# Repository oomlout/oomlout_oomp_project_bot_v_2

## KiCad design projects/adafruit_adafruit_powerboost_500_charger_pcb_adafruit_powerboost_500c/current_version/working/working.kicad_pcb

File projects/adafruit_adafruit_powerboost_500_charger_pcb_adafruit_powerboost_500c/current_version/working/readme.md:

# adafruit_powerboost_500_charger_pcb
 
## summary 
* id: adafruit_adafruit_powerboost_500_charger_pcb_adafruit_powerboost_500c
* user: adafruit
* name: adafruit_powerboost_500_charger_pcb
* board: adafruit_powerboost_500c
* repo: https://github.com/adafruit/Adafruit-PowerBoost-500-Charger-PCB

* src_file_repo_sch: 
* src_file_repo_sch_link: https://github.com/adafruit/Adafruit-PowerBoost-500-Charger-PCB/tree/master/
* full details link: https://github.com/oomlout/oomlout_oomp_project_bot_v_2/tree/main/projects/adafruit_adafruit_powerboost_500_charger_pcb_adafruit_powerboost_500c/current_version/working  

## schematic  
  
[schematic (pdf)](working_schematic.pdf) 

## pcb  

[board (pdf)](working.pdf)  

## working_bom
| Id | Designator | Footprint | Quantity | Designation | Supplier and ref |  | None | 
| --- | --- | --- | --- | --- | --- | --- | --- | 
| 1 | U$26 | SYMBOL_MINUS | 1 |  |  |  | [''] | 
| 2 | R3,R1 | 0805-NO | 2 | 1.87Mohm |  |  | [''] | 
| 3 | U$13,U$25 | SYMBOL_PLUS | 2 |  |  |  | [''] | 
| 4 | R13,R2 | 0805-NO | 2 | 340K |  |  | [''] | 
| 5 | U$12,U$10 | MOUNTINGHOLE_2.5_PLATED | 2 | MOUNTINGHOLE2.5 |  |  | [''] | 
| 6 | R6 | 0805-NO | 1 | 470 |  |  | [''] | 
| 7 | R10,R12 | 0805-NO | 2 | 49.9K 1% |  |  | [''] | 
| 8 | FID3,FID2 | FIDUCIAL_1MM | 2 | FIDUCIAL" |  |  | [''] | 
| 9 | C2 | 0805-NO | 1 | 2.2uF |  |  | [''] | 
| 10 | PWR0 | CHIPLED_0805_NOOUTLINE | 1 | BLUE |  |  | [''] | 
| 11 | C6 | 0805-NO | 1 | 10ÂµF |  |  | [''] | 
| 12 | LED4 | CHIPLED_0805_NOOUTLINE | 1 | GREEN |  |  | [''] | 
| 13 | R9,R11 | 0805-NO | 2 | 75K 1% |  |  | [''] | 
| 14 | Q1 | SC59-BEC | 1 | MMUN2133LT1G |  |  | [''] | 
| 15 | R7,R20,R5 | 0805-NO | 3 | 1K |  |  | [''] | 
| 16 | U1 | PVQFN-16 | 1 | TPS61090RSAR |  |  | [''] | 
| 17 | B1 | JSTPH2 | 1 | 1.8-5V |  |  | [''] | 
| 18 | U2 | SOT23-5 | 1 | MCP73831T-2ACI/OT |  |  | [''] | 
| 19 | X2 | 4UCONN_20329 | 1 | microUSB |  |  | [''] | 
| 20 | C5 | EIA3528-21_B-R | 1 | 100uF/6V |  |  | [''] | 
| 21 | R4 | 0805-NO | 1 | 200K |  |  | [''] | 
| 22 | JP1 | 1X06-CLEANBIG | 1 |  |  |  | [''] | 
| 23 | JP2 | 1X02_ROUND | 1 |  |  |  | [''] | 
| 24 | R8 | 0805-NO | 1 | 2k |  |  | [''] | 
| 25 | CN1 | USB_HOST-PTH | 1 | USBA_FEMALE |  |  | [''] | 
| 26 | LBO0 | CHIPLED_0805_NOOUTLINE | 1 | RED |  |  | [''] | 
| 27 | L1 | INDUCTOR_5X5MM_TDK_VLC5045 | 1 | VLC5045-6.8uH |  |  | [''] | 
| 28 | U$28 | ADAFRUIT_2.5MM | 1 |  |  |  | [''] | 
| 29 | C4 | 0805-NO | 1 | 0.1uF |  |  | [''] | 
| 30 | C1 | 0805-NO | 1 | 10uF |  |  | [''] | 
| 31 | LED3 | CHIPLED_0805_NOOUTLINE | 1 | ORANGE |  |  | [''] | 
| 32 | X1 | TERMBLOCK_1X2-3.5MM | 1 |  |  |  | [''] | 
| 33 | U$29 | ADAFRUIT_5MM | 1 |  |  |  | [''] | 

## bom_schematic
| Ref | Qnty | Value | Cmp name | Footprint | Description | Vendor | DNP | 
| --- | --- | --- | --- | --- | --- | --- | --- | 
| B1 | 1 | 1.8-5V | BATTERY | working:JSTPH2 |  |  |  | 
| C1 | 1 | 10uF | CAP_CERAMIC0805-NOOUTLINE | working:0805-NO |  |  |  | 
| C2 | 1 | 2.2uF | CAP_CERAMIC0805-NOOUTLINE | working:0805-NO |  |  |  | 
| C4 | 1 | 0.1uF | CAP_CERAMIC0805-NOOUTLINE | working:0805-NO |  |  |  | 
| C5 | 1 | 100uF/6V | CAP_TANTALUMB/3528_REFLOW | working:EIA3528-21_B-R |  |  |  | 
| C6 | 1 | 10ÂµF | CAP_CERAMIC0805-NOOUTLINE | working:0805-NO |  |  |  | 
| CN1 | 1 | USBA_FEMALE | USB_TYPEAPTHFML | working:USB_HOST-PTH |  |  |  | 
| FID2, FID3 | 2 | FIDUCIAL"" | FIDUCIAL{dblquote}{dblquote} | working:FIDUCIAL_1MM |  |  |  | 
| JP1 | 1 | PINHD-1X6CB | PINHD-1X6CB | working:1X06-CLEANBIG |  |  |  | 
| JP2 | 1 | HEADER-1X2ROUND | HEADER-1X2ROUND | working:1X02_ROUND |  |  |  | 
| L1 | 1 | VLC5045-6.8uH | INDUCTORTDK_VLC5045 | working:INDUCTOR_5X5MM_TDK_VLC5045 |  |  |  | 
| LBO0 | 1 | RED | LED0805_NOOUTLINE | working:CHIPLED_0805_NOOUTLINE |  |  |  | 
| LED3 | 1 | ORANGE | LED0805_NOOUTLINE | working:CHIPLED_0805_NOOUTLINE |  |  |  | 
| LED4 | 1 | GREEN | LED0805_NOOUTLINE | working:CHIPLED_0805_NOOUTLINE |  |  |  | 
| PWR0 | 1 | BLUE | LED0805_NOOUTLINE | working:CHIPLED_0805_NOOUTLINE |  |  |  | 
| Q1 | 1 | MMUN2133LT1G | -PNP_DRIVER-SC59-BEC | working:SC59-BEC |  |  |  | 
| R1, R3 | 2 | 1.87Mohm | RESISTOR0805_NOOUTLINE | working:0805-NO |  |  |  | 
| R2, R13 | 2 | 340K | RESISTOR0805_NOOUTLINE | working:0805-NO |  |  |  | 
| R4 | 1 | 200K | RESISTOR0805_NOOUTLINE | working:0805-NO |  |  |  | 
| R5, R7, R20 | 3 | 1K | RESISTOR0805_NOOUTLINE | working:0805-NO |  |  |  | 
| R6 | 1 | 470 | RESISTOR0805_NOOUTLINE | working:0805-NO |  |  |  | 
| R8 | 1 | 2k | RESISTOR0805_NOOUTLINE | working:0805-NO |  |  |  | 
| R9, R11 | 2 | 75K 1% | RESISTOR0805_NOOUTLINE | working:0805-NO |  |  |  | 
| R10, R12 | 2 | 49.9K 1% | RESISTOR0805_NOOUTLINE | working:0805-NO |  |  |  | 
| U1 | 1 | TPS61090RSAR | VREG_TPS6103X | working:PVQFN-16 |  |  |  | 
| U2 | 1 | MCP73831T-2ACI/OT | MCP73831/2 | working:SOT23-5 |  |  |  | 
| U$10, U$12 | 2 | MOUNTINGHOLE2.5 | MOUNTINGHOLE2.5 | working:MOUNTINGHOLE_2.5_PLATED |  |  |  | 
| X1 | 1 | TERMBLOCK_1X2 | TERMBLOCK_1X2 | working:TERMBLOCK_1X2-3.5MM |  |  |  | 
| X2 | 1 | microUSB | USBMICRO_20329 | working:4UCONN_20329 |  |  |  | 

## mounting_holes
| x | y | package | value | ref | size | 
| --- | --- | --- | --- | --- | --- | 
| 0.0 | 16.51 | MOUNTINGHOLE_2.5_PLATED | MOUNTINGHOLE2.5 | U$10 | m3 | 
| 0.0 | 0.0 | MOUNTINGHOLE_2.5_PLATED | MOUNTINGHOLE2.5 | U$12 | m3 |

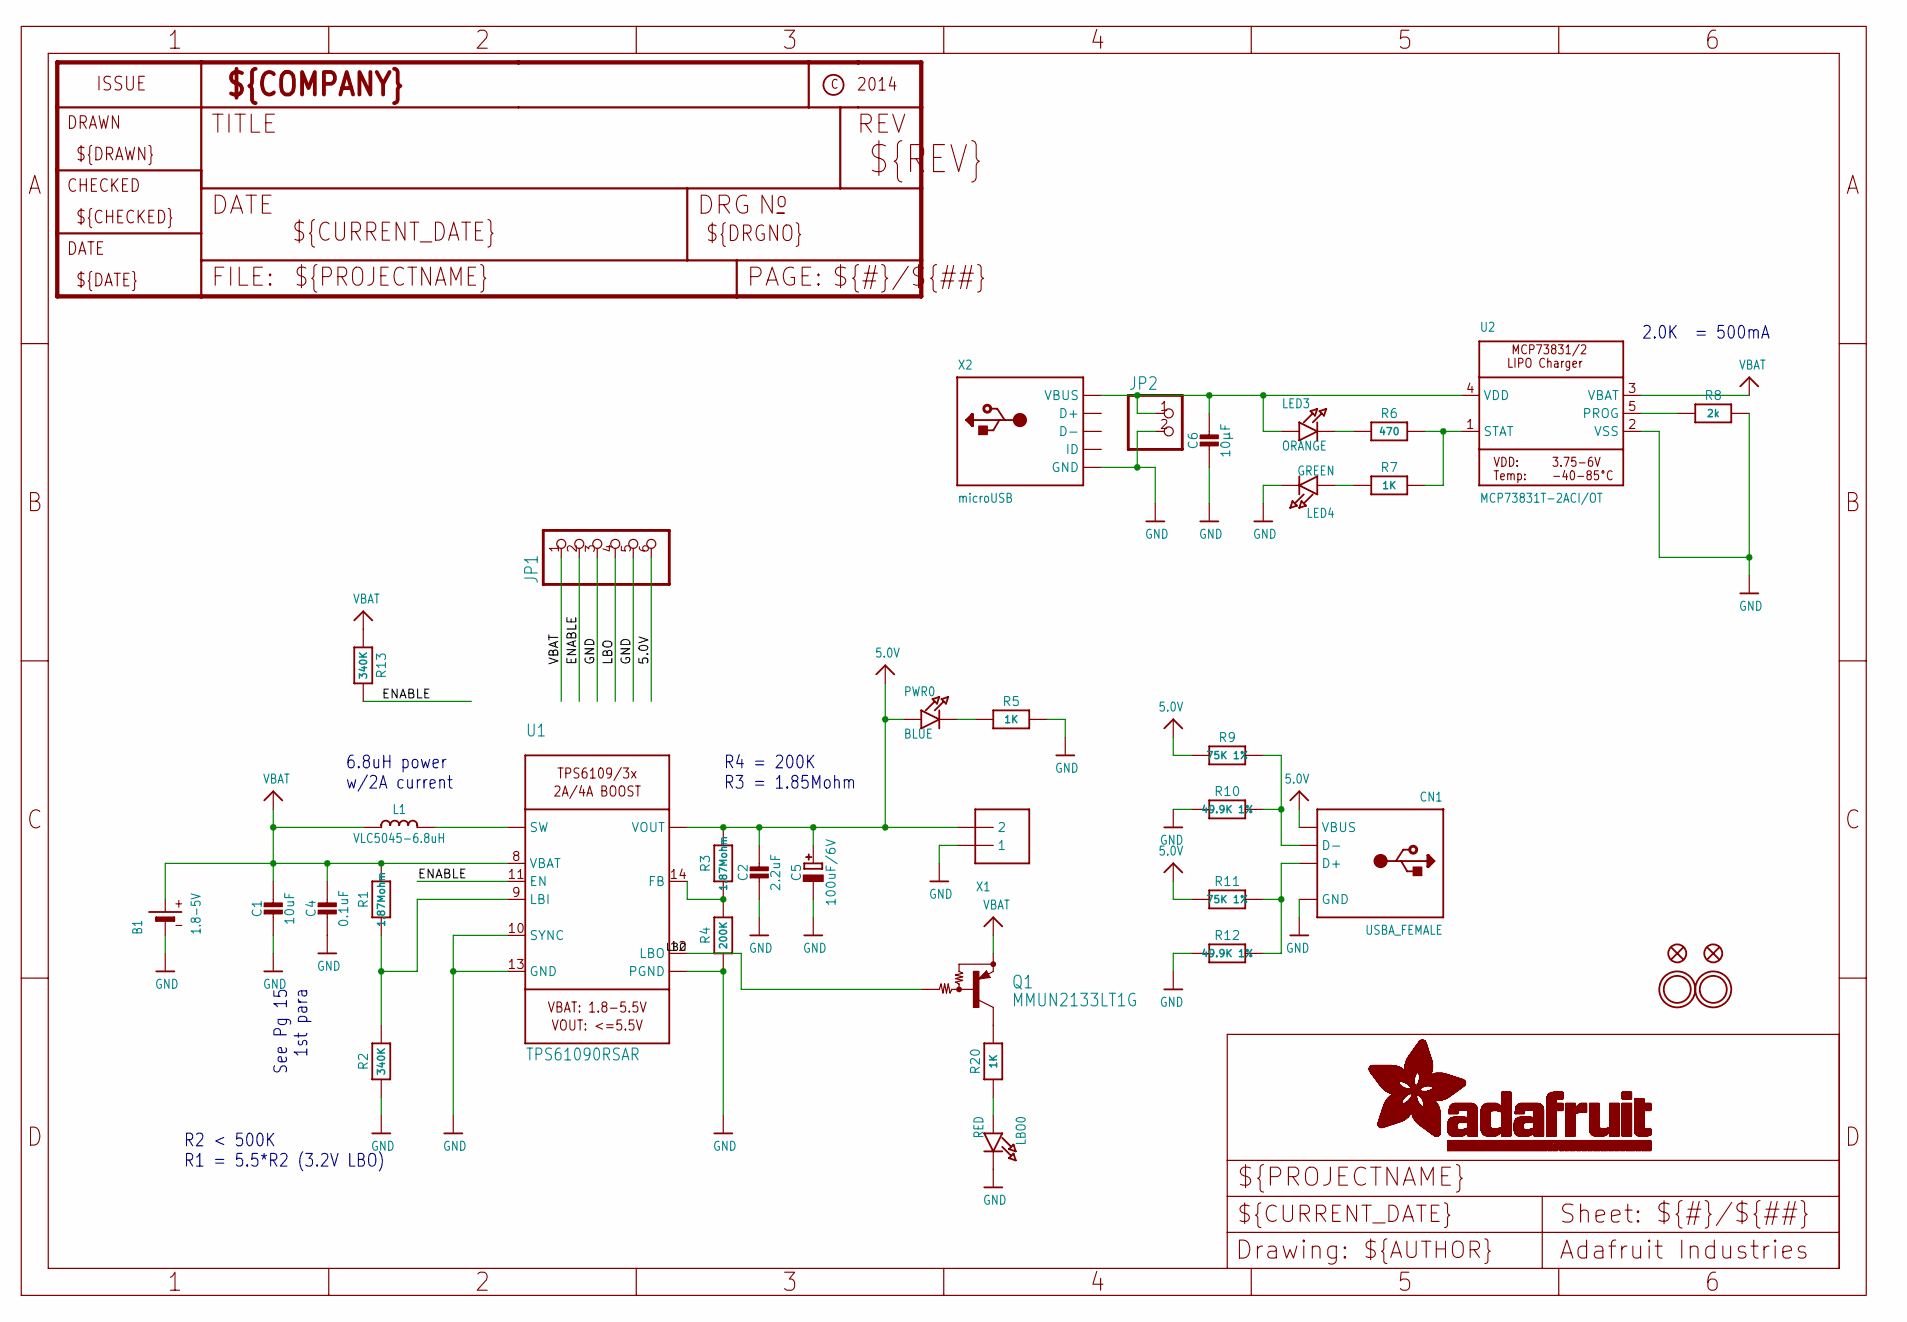
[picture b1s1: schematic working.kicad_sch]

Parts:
B1: 1.8-5V; JSTPH2
C1: 10uF; 0805-NO
C2: 2.2uF; 0805-NO
C4: 0.1uF; 0805-NO
C5: 100uF/6V; EIA3528-21_B-R
C6: 10µF; 0805-NO
CN1: USBA_FEMALE; USB_HOST-PTH
FID2, FID3: FIDUCIAL""; FIDUCIAL_1MM
JP1: PINHD-1X6CB; 1X06-CLEANBIG
JP2: HEADER-1X2ROUND; 1X02_ROUND
L1: VLC5045-6.8uH; INDUCTOR_5X5MM_TDK_VLC5045
LBO0: RED; CHIPLED_0805_NOOUTLINE
LED3: ORANGE; CHIPLED_0805_NOOUTLINE
LED4: GREEN; CHIPLED_0805_NOOUTLINE
PWR0: BLUE; CHIPLED_0805_NOOUTLINE
Q1: MMUN2133LT1G; SC59-BEC
R1, R3: 1.87Mohm; 0805-NO
R2, R13: 340K; 0805-NO
R4: 200K; 0805-NO
R5, R7, R20: 1K; 0805-NO
R6: 470; 0805-NO
R8: 2k; 0805-NO
R9, R11: 75K 1%; 0805-NO
R10, R12: 49.9K 1%; 0805-NO
U1: TPS61090RSAR; PVQFN-16
U2: MCP73831T-2ACI/OT; SOT23-5
U$10, U$12: MOUNTINGHOLE2.5; MOUNTINGHOLE_2.5_PLATED
X1: TERMBLOCK_1X2; TERMBLOCK_1X2-3.5MM
X2: microUSB; 4UCONN_20329

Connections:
5.0V: C2.1, C5.+, CN1.VBUS, JP1.6, PWR0.A, R3.2, R9.2, R11.2, U1.1 (VOUT), U1.15 (VOUT), U1.16 (VOUT), X1.2
D+: CN1.D+, R11.1, R12.1
D-: CN1.D-, R9.1, R10.1
ENABLE: JP1.2, R13.2, U1.11 (EN)
GND: B1.1 (-), C1.2, C2.2, C4.2, C5.-, C6.2, CN1.GND, JP1.3, JP1.5, JP2.2, LBO0.C, LED4.C, R2.1, R4.1, R5.2, R8.2, R10.2, R12.2, U1.5 (PGND), U1.6 (PGND), U1.7 (PGND), U1.10 (SYNC), U1.13 (GND), U1.P$18 (PGND), U1.P$19 (PGND), U1.P$20 (PGND), U1.P$21 (PGND), U1.P$22 (PGND), U1.THERMAL (PGND), U2.2 (VSS), X1.1, X2.BASE@1 (GND), X2.BASE@2 (GND), X2.GND, X2.SPRT@1 (GND), X2.SPRT@2 (GND), X2.SPRT@3 (GND), X2.SPRT@4 (GND)
LBO: JP1.4, Q1.B, U1.12 (LBO)
unnamed: L1.P$2 (2), U1.3 (SW), U1.4 (SW)
unnamed: LBO0.A, R20.1
unnamed: R1.1, R2.2, U1.9 (LBI)
unnamed: PWR0.C, R5.1
unnamed: R3.1, R4.2, U1.14 (FB)
unnamed: LED3.C, R6.1
unnamed: R6.2, R7.2, U2.1 (STAT)
unnamed: R8.1, U2.5 (PROG)
unnamed: LED4.A, R7.1
unnamed: Q1.C, R20.2
VBAT: B1.2 (+), C1.1, C4.1, JP1.1, L1.P$1 (1), Q1.E, R1.2, R13.1, U1.8 (VBAT), U2.3 (VBAT)
VDD1: C6.1, JP2.1, LED3.A, U2.4 (VDD), X2.VBUS

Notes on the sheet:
2.0K = 500mA
R4 = 200K R3 = 1.85Mohm
6.8uH power w/2A current
See Pg 15 1st para
R2 < 500K R1 = 5.5*R2 (3.2V LBO)

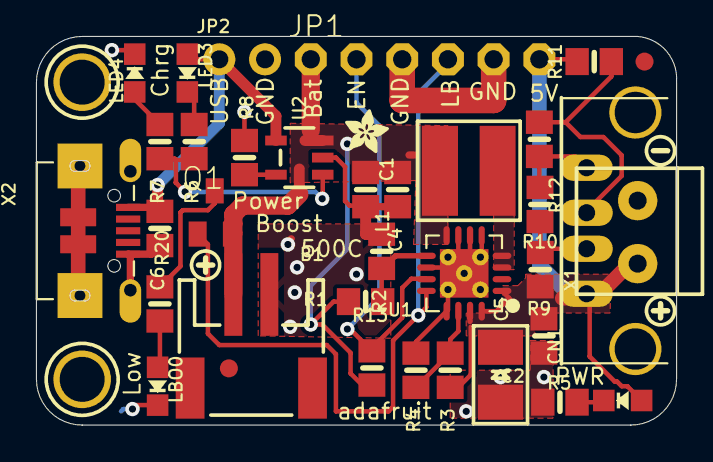
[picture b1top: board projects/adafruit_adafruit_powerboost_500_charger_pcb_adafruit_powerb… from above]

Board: 2 copper layers, 35.6 x 21.6 mm, 42 parts (1 on the bottom side), 18 nets.

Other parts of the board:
U$13, U$25: SYMBOL_PLUS
U$26: SYMBOL_MINUS
U$28: ADAFRUIT_2.5MM
U$29: ADAFRUIT_5MM

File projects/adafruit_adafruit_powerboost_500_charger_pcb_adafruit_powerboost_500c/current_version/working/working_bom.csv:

"Id";"Designator";"Footprint";"Quantity";"Designation";"Supplier and ref";
1;"U$26";"SYMBOL_MINUS";1;"";;;
2;"R3,R1";"0805-NO";2;"1.87Mohm";;;
3;"U$13,U$25";"SYMBOL_PLUS";2;"";;;
4;"R13,R2";"0805-NO";2;"340K";;;
5;"U$12,U$10";"MOUNTINGHOLE_2.5_PLATED";2;"MOUNTINGHOLE2.5";;;
6;"R6";"0805-NO";1;"470";;;
7;"R10,R12";"0805-NO";2;"49.9K 1%";;;
8;"FID3,FID2";"FIDUCIAL_1MM";2;"FIDUCIAL""";;;
9;"C2";"0805-NO";1;"2.2uF";;;
10;"PWR0";"CHIPLED_0805_NOOUTLINE";1;"BLUE";;;
11;"C6";"0805-NO";1;"10µF";;;
12;"LED4";"CHIPLED_0805_NOOUTLINE";1;"GREEN";;;
13;"R9,R11";"0805-NO";2;"75K 1%";;;
14;"Q1";"SC59-BEC";1;"MMUN2133LT1G";;;
15;"R7,R20,R5";"0805-NO";3;"1K";;;
16;"U1";"PVQFN-16";1;"TPS61090RSAR";;;
17;"B1";"JSTPH2";1;"1.8-5V";;;
18;"U2";"SOT23-5";1;"MCP73831T-2ACI/OT";;;
19;"X2";"4UCONN_20329";1;"microUSB";;;
20;"C5";"EIA3528-21_B-R";1;"100uF/6V";;;
21;"R4";"0805-NO";1;"200K";;;
22;"JP1";"1X06-CLEANBIG";1;"";;;
23;"JP2";"1X02_ROUND";1;"";;;
24;"R8";"0805-NO";1;"2k";;;
25;"CN1";"USB_HOST-PTH";1;"USBA_FEMALE";;;
26;"LBO0";"CHIPLED_0805_NOOUTLINE";1;"RED";;;
27;"L1";"INDUCTOR_5X5MM_TDK_VLC5045";1;"VLC5045-6.8uH";;;
28;"U$28";"ADAFRUIT_2.5MM";1;"";;;
29;"C4";"0805-NO";1;"0.1uF";;;
30;"C1";"0805-NO";1;"10uF";;;
31;"LED3";"CHIPLED_0805_NOOUTLINE";1;"ORANGE";;;
32;"X1";"TERMBLOCK_1X2-3.5MM";1;"";;;
33;"U$29";"ADAFRUIT_5MM";1;"";;;

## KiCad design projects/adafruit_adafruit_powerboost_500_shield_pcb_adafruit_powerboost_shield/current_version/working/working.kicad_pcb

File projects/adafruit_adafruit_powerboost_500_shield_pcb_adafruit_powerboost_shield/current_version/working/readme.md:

# adafruit_powerboost_500_shield_pcb
 
## summary 
* id: adafruit_adafruit_powerboost_500_shield_pcb_adafruit_powerboost_shield
* user: adafruit
* name: adafruit_powerboost_500_shield_pcb
* board: adafruit_powerboost_shield
* repo: https://github.com/adafruit/Adafruit-PowerBoost-500-Shield-PCB

* src_file_repo_sch: 
* src_file_repo_sch_link: https://github.com/adafruit/Adafruit-PowerBoost-500-Shield-PCB/tree/master/
* full details link: https://github.com/oomlout/oomlout_oomp_project_bot_v_2/tree/main/projects/adafruit_adafruit_powerboost_500_shield_pcb_adafruit_powerboost_shield/current_version/working  

## schematic  
  
[schematic (pdf)](working_schematic.pdf) 

## pcb  

[board (pdf)](working.pdf)  

## working_bom
| Id | Designator | Footprint | Quantity | Designation | Supplier and ref |  | None | 
| --- | --- | --- | --- | --- | --- | --- | --- | 
| 1 | LED3 | CHIPLED_0805_NOOUTLINE | 1 | BLUE |  |  | [''] | 
| 2 | R9,R14 | 0805-NO | 2 | 1.87Mohm |  |  | [''] | 
| 3 | R11,R23 | 0805-NO | 2 | 340K |  |  | [''] | 
| 4 | @HOLE0,@HOLE1,@HOLE2 |  | 3 |  |  |  | [''] | 
| 5 | S1 | OS102011MA1Q | 1 | OS102011MA1Q |  |  | [''] | 
| 6 | LED1 | CHIPLED_0805_NOOUTLINE | 1 | YELLOW |  |  | [''] | 
| 7 | D1 | SOD-123 | 1 | MBR120 |  |  | [''] | 
| 8 | U4 | PVQFN-16 | 1 | TPS61030RSAR |  |  | [''] | 
| 9 | R10 | 0805-NO | 1 | 200K |  |  | [''] | 
| 10 | T1 | SC59-BEC | 1 | MMUN2133LT1G |  |  | [''] | 
| 11 | C9 | EIA3528-21_B-R | 1 | 100uF/6V |  |  | [''] | 
| 12 | R5,R20,R3 | 0805-NO | 3 | 1K |  |  | [''] | 
| 13 | R1 | 0805-NO | 1 | 470 |  |  | [''] | 
| 14 | U$4,U$3 | FIDUCIAL_1MM | 2 | FIDUCIAL |  |  | [''] | 
| 15 | R4,R2 | 0805-NO | 2 | 2K |  |  | [''] | 
| 16 | C4 | 0805-NO | 1 | 10ÂµF |  |  | [''] | 
| 17 | U$6 | ADAFRUIT_TEXT_30MM | 1 |  |  |  | [''] | 
| 18 | F1 | R1206 | 1 | 500mA |  |  | [''] | 
| 19 | L1 | INDUCTOR_5X5MM_TDK_VLC5045 | 1 | VLC5045-6.8uH |  |  | [''] | 
| 20 | X1 | 4UCONN_20329 | 1 | MicroUSB |  |  | [''] | 
| 21 | C8 | 0805-NO | 1 | 0.1uF |  |  | [''] | 
| 22 | ANALOG0 | 1X06 | 1 | ANALOG |  |  | [''] | 
| 23 | LED2 | CHIPLED_0805_NOOUTLINE | 1 | GREEN |  |  | [''] | 
| 24 | U3 | SOT23-5 | 1 | MCP73831T-2ACI/OT |  |  | [''] | 
| 25 | C6 | 0805-NO | 1 | 10uF |  |  | [''] | 
| 26 | U2 | ARDUINOR3-NOSILK | 1 | ARDUINOR3-NOSILK |  |  | [''] | 
| 27 | SW1 | KMR2 | 1 | SPST_TACT-KMR2 |  |  | [''] | 
| 28 | BATT_IN0 | JST-PH-2-SMT | 1 | JST-PH |  |  | [''] | 
| 29 | LED4 | CHIPLED_0805_NOOUTLINE | 1 | RED |  |  | [''] | 
| 30 | C7 | 0805-NO | 1 | 2.2uF |  |  | [''] | 
| 31 | SJ2,SJ1,SJ6,SJ4,SJ5,SJ3 | SOLDERJUMPER_ARROW_NOPASTE | 6 |  |  |  | [''] | 

## bom_schematic
| Ref | Qnty | Value | Cmp name | Footprint | Description | Vendor | DNP | 
| --- | --- | --- | --- | --- | --- | --- | --- | 
| ANALOG0 | 1 | ANALOG | PINHD-1X6 | working:1X06 |  |  |  | 
| BATT_IN0 | 1 | JST-PH | JST_2PIN-SMT | working:JST-PH-2-SMT |  |  |  | 
| C4 | 1 | 10ÂµF | CAP_CERAMIC0805-NOOUTLINE | working:0805-NO |  |  |  | 
| C6 | 1 | 10uF | CAP_CERAMIC0805-NOOUTLINE | working:0805-NO |  |  |  | 
| C7 | 1 | 2.2uF | CAP_CERAMIC0805-NOOUTLINE | working:0805-NO |  |  |  | 
| C8 | 1 | 0.1uF | CAP_CERAMIC0805-NOOUTLINE | working:0805-NO |  |  |  | 
| C9 | 1 | 100uF/6V | CAP_TANTALUMB/3528_REFLOW | working:EIA3528-21_B-R |  |  |  | 
| D1 | 1 | MBR120 | DIODE-SCHOTTKYSOD-123 | working:SOD-123 |  |  |  | 
| F1 | 1 | 500mA | PTCFUSE-1206 | working:R1206 |  |  |  | 
| L1 | 1 | VLC5045-6.8uH | INDUCTORTDK_VLC5045 | working:INDUCTOR_5X5MM_TDK_VLC5045 |  |  |  | 
| LED1 | 1 | YELLOW | LED0805_NOOUTLINE | working:CHIPLED_0805_NOOUTLINE |  |  |  | 
| LED2 | 1 | GREEN | LED0805_NOOUTLINE | working:CHIPLED_0805_NOOUTLINE |  |  |  | 
| LED3 | 1 | BLUE | LED0805_NOOUTLINE | working:CHIPLED_0805_NOOUTLINE |  |  |  | 
| LED4 | 1 | RED | LED0805_NOOUTLINE | working:CHIPLED_0805_NOOUTLINE |  |  |  | 
| R1 | 1 | 470 | RESISTOR0805_NOOUTLINE | working:0805-NO |  |  |  | 
| R2, R4 | 2 | 2K | RESISTOR0805_NOOUTLINE | working:0805-NO |  |  |  | 
| R3, R5, R20 | 3 | 1K | RESISTOR0805_NOOUTLINE | working:0805-NO |  |  |  | 
| R9, R14 | 2 | 1.87Mohm | RESISTOR0805_NOOUTLINE | working:0805-NO |  |  |  | 
| R10 | 1 | 200K | RESISTOR0805_NOOUTLINE | working:0805-NO |  |  |  | 
| R11, R23 | 2 | 340K | RESISTOR0805_NOOUTLINE | working:0805-NO |  |  |  | 
| S1 | 1 | OS102011MA1Q | OS102011MA1Q | working:OS102011MA1Q |  |  |  | 
| SJ1, SJ2, SJ3, SJ4, SJ5, SJ6 | 6 | SOLDERJUMPER | SOLDERJUMPER | working:SOLDERJUMPER_ARROW_NOPASTE |  |  |  | 
| SW1 | 1 | SPST_TACT-KMR2 | SPST_TACT-KMR2 | working:KMR2 |  |  |  | 
| T1 | 1 | MMUN2133LT1G | -PNP_DRIVER-SC59-BEC | working:SC59-BEC |  |  |  | 
| U2 | 1 | ARDUINOR3-NOSILK | ARDUINOR3-NOSILK | working:ARDUINOR3-NOSILK |  |  |  | 
| U3 | 1 | MCP73831T-2ACI/OT | MCP73831/2 | working:SOT23-5 |  |  |  | 
| U4 | 1 | TPS61030RSAR | VREG_TPS6103X | working:PVQFN-16 |  |  |  | 
| U$3, U$4 | 2 | FIDUCIAL | FIDUCIAL | working:FIDUCIAL_1MM |  |  |  | 
| X1 | 1 | MicroUSB | USBMICRO_20329 | working:4UCONN_20329 |  |  |  |

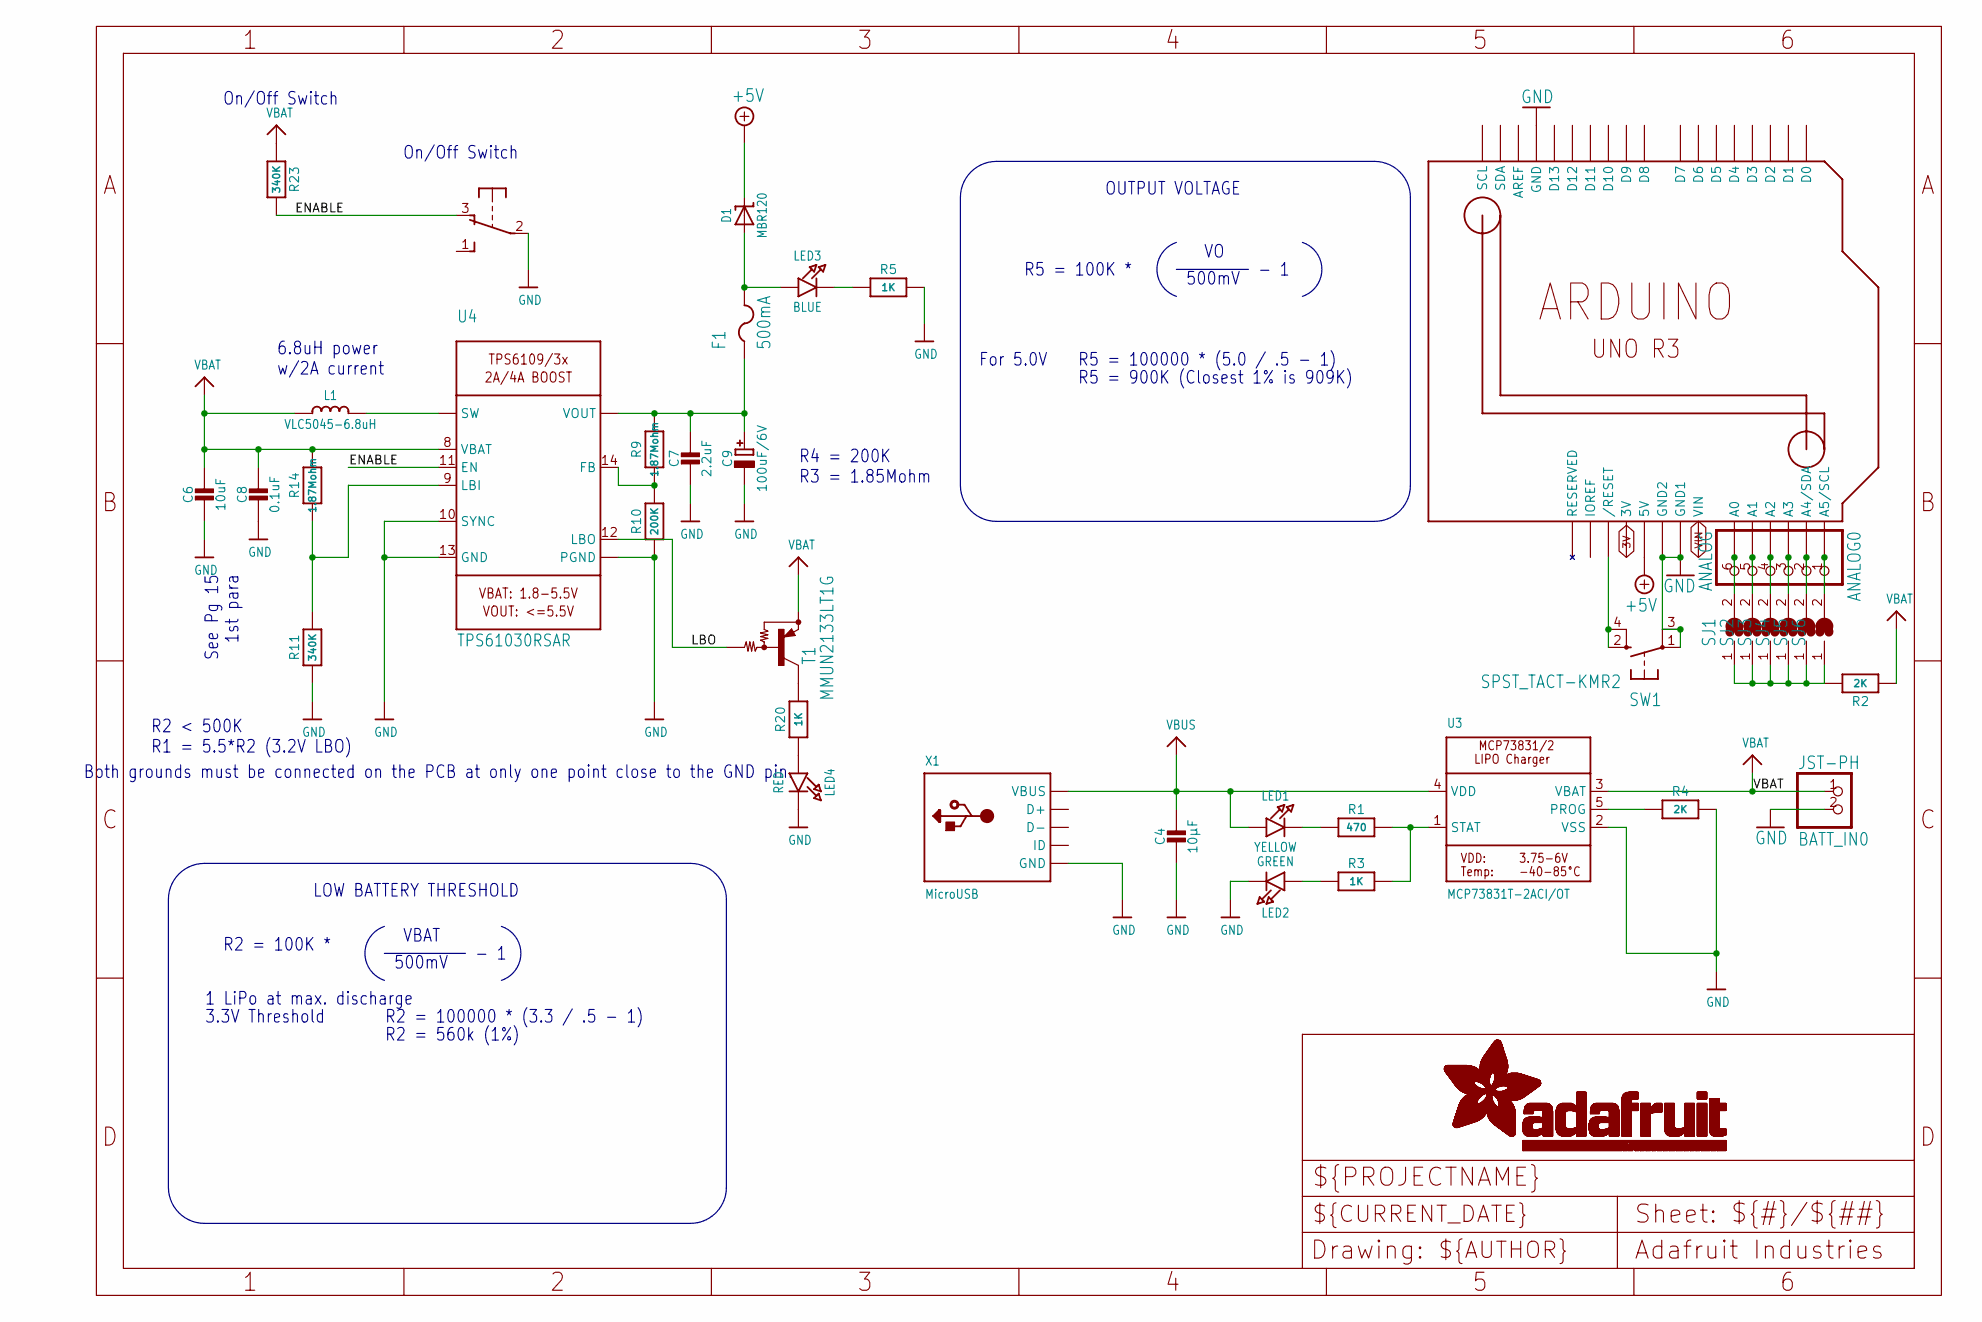
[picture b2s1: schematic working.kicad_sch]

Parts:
ANALOG0: ANALOG; 1X06
BATT_IN0: JST-PH; JST-PH-2-SMT
C4: 10µF; 0805-NO
C6: 10uF; 0805-NO
C7: 2.2uF; 0805-NO
C8: 0.1uF; 0805-NO
C9: 100uF/6V; EIA3528-21_B-R
D1: MBR120; SOD-123
F1: 500mA; R1206
L1: VLC5045-6.8uH; INDUCTOR_5X5MM_TDK_VLC5045
LED1: YELLOW; CHIPLED_0805_NOOUTLINE
LED2: GREEN; CHIPLED_0805_NOOUTLINE
LED3: BLUE; CHIPLED_0805_NOOUTLINE
LED4: RED; CHIPLED_0805_NOOUTLINE
R1: 470; 0805-NO
R2, R4: 2K; 0805-NO
R3, R5, R20: 1K; 0805-NO
R9, R14: 1.87Mohm; 0805-NO
R10: 200K; 0805-NO
R11, R23: 340K; 0805-NO
S1: OS102011MA1Q
SJ1, SJ2, SJ3, SJ4, SJ5, SJ6: SOLDERJUMPER; SOLDERJUMPER_ARROW_NOPASTE
SW1: SPST_TACT-KMR2; KMR2
T1: MMUN2133LT1G; SC59-BEC
U2: ARDUINOR3-NOSILK
U3: MCP73831T-2ACI/OT; SOT23-5
U4: TPS61030RSAR; PVQFN-16
U$3, U$4: FIDUCIAL; FIDUCIAL_1MM
X1: MicroUSB; 4UCONN_20329

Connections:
3V: U2.3V
+5V: D1.C, U2.5V
A0: ANALOG0.6, SJ1.2, U2.A0
A1: ANALOG0.5, SJ2.2, U2.A1
A2: ANALOG0.4, SJ3.2, U2.A2
A3: ANALOG0.3, SJ4.2, U2.A3
A4: ANALOG0.2, SJ5.2, U2.A4 (A4/SDA)
A5: ANALOG0.1, SJ6.2, U2.A5 (A5/SCL)
ENABLE: R23.2, S1.3 (O), U4.11 (EN)
FB: R9.1, R10.2, U4.14 (FB)
GND: BATT_IN0.2 (1), C4.2, C6.2, C7.2, C8.2, C9.-, LED2.C, LED4.C, R4.2, R5.2, R10.1, R11.1, S1.2, SW1.1, SW1.3 (P1), U2.GND, U2.GND1, U2.GND2, U3.2 (VSS), U4.5 (PGND), U4.6 (PGND), U4.7 (PGND), U4.10 (SYNC), U4.13 (GND), U4.P$18 (PGND), U4.P$19 (PGND), U4.P$20 (PGND), U4.P$21 (PGND), U4.P$22 (PGND), U4.THERMAL (PGND), X1.BASE@1 (GND), X1.BASE@2 (GND), X1.GND, X1.SPRT@1 (GND), X1.SPRT@2 (GND), X1.SPRT@3 (GND), X1.SPRT@4 (GND)
LBI: R11.2, R14.1, U4.9 (LBI)
LBO: T1.B, U4.12 (LBO)
unnamed: R2.2, SJ1.1, SJ2.1, SJ3.1, SJ4.1, SJ5.1, SJ6.1
unnamed: LED1.C, R1.1
unnamed: R1.2, R3.2, U3.1 (STAT)
unnamed: L1.P$2 (2), U4.3 (SW), U4.4 (SW)
unnamed: R4.1, U3.5 (PROG)
unnamed: LED2.A, R3.1
unnamed: LED3.C, R5.1
unnamed: LED4.A, R20.1
unnamed: R20.2, T1.C
unnamed: D1.A, F1.2, LED3.A
RESET: SW1.2 (S), SW1.4 (S1), U2.RESET (/RESET)
VBAT: BATT_IN0.1 (2), C6.1, C8.1, L1.P$1 (1), R2.1, R14.2, R23.1, T1.E, U3.3 (VBAT), U4.8 (VBAT)
VBUS: C4.1, LED1.A, U3.4 (VDD), X1.VBUS
VIN: U2.VIN
VOUT: C7.1, C9.+, F1.1, R9.2, U4.1 (VOUT), U4.15 (VOUT), U4.16 (VOUT)

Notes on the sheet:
3.3V Threshold
R2 < 500K R1 = 5.5*R2 (3.2V LBO)
R5 = 100K *
6.8uH power w/2A current
R4 = 200K R3 = 1.85Mohm
- 1
On/Off Switch
VBAT
LOW BATTERY THRESHOLD
OUTPUT VOLTAGE
For 5.0V
R2 = 560k (1%)
500mV
R5 = 100000 * (5.0 / .5 - 1)
See Pg 15 1st para
R2 = 100K *
R5 = 900K (Closest 1% is 909K)
Both grounds must be connected on the PCB at only one point close to the GND pin.
1 LiPo at max. discharge
R2 = 100000 * (3.3 / .5 - 1)

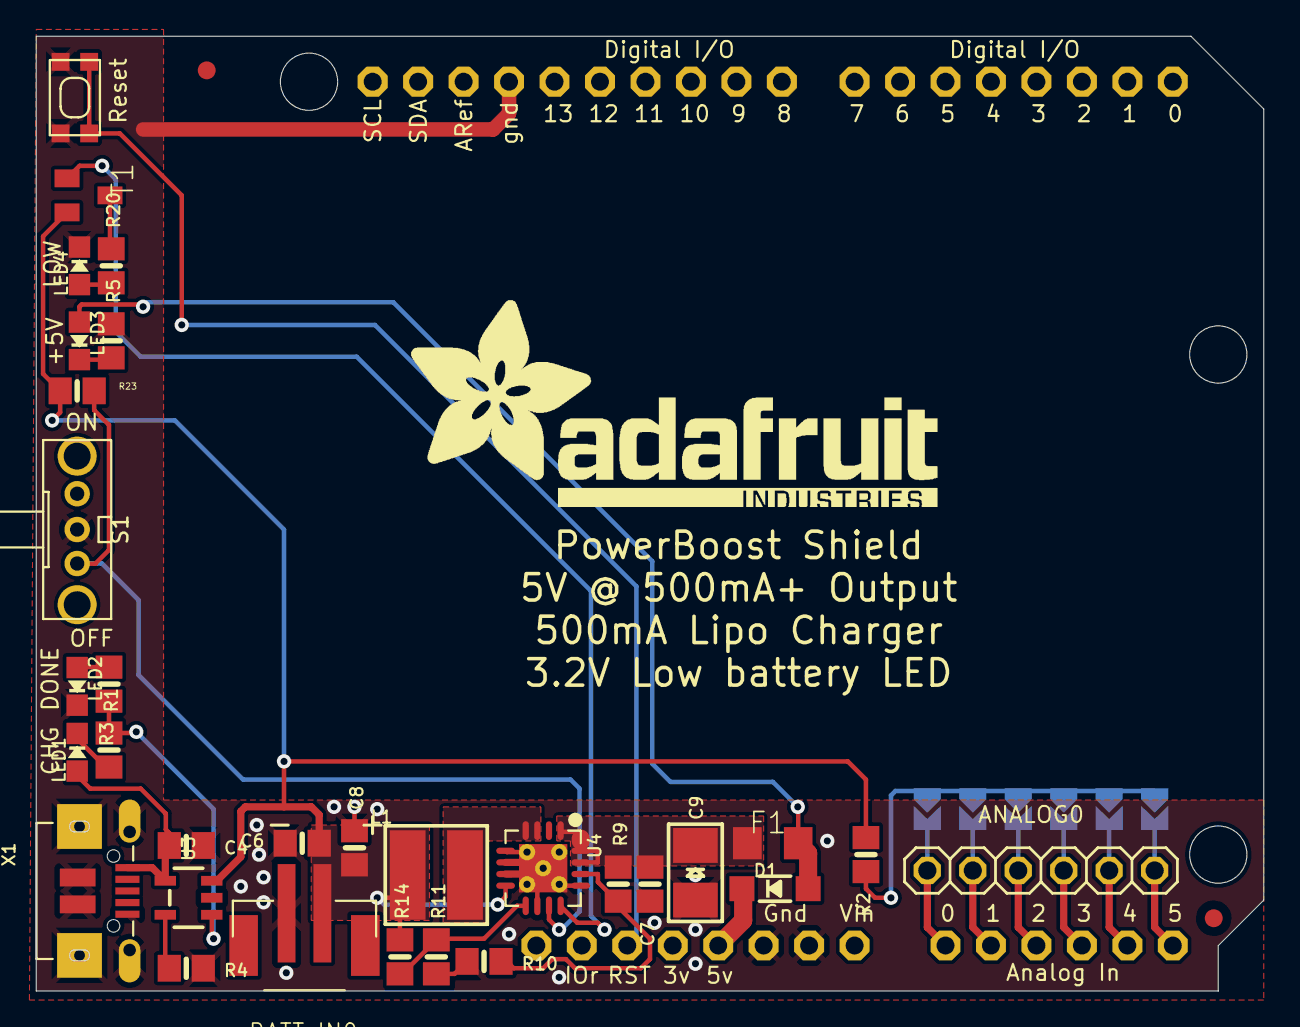
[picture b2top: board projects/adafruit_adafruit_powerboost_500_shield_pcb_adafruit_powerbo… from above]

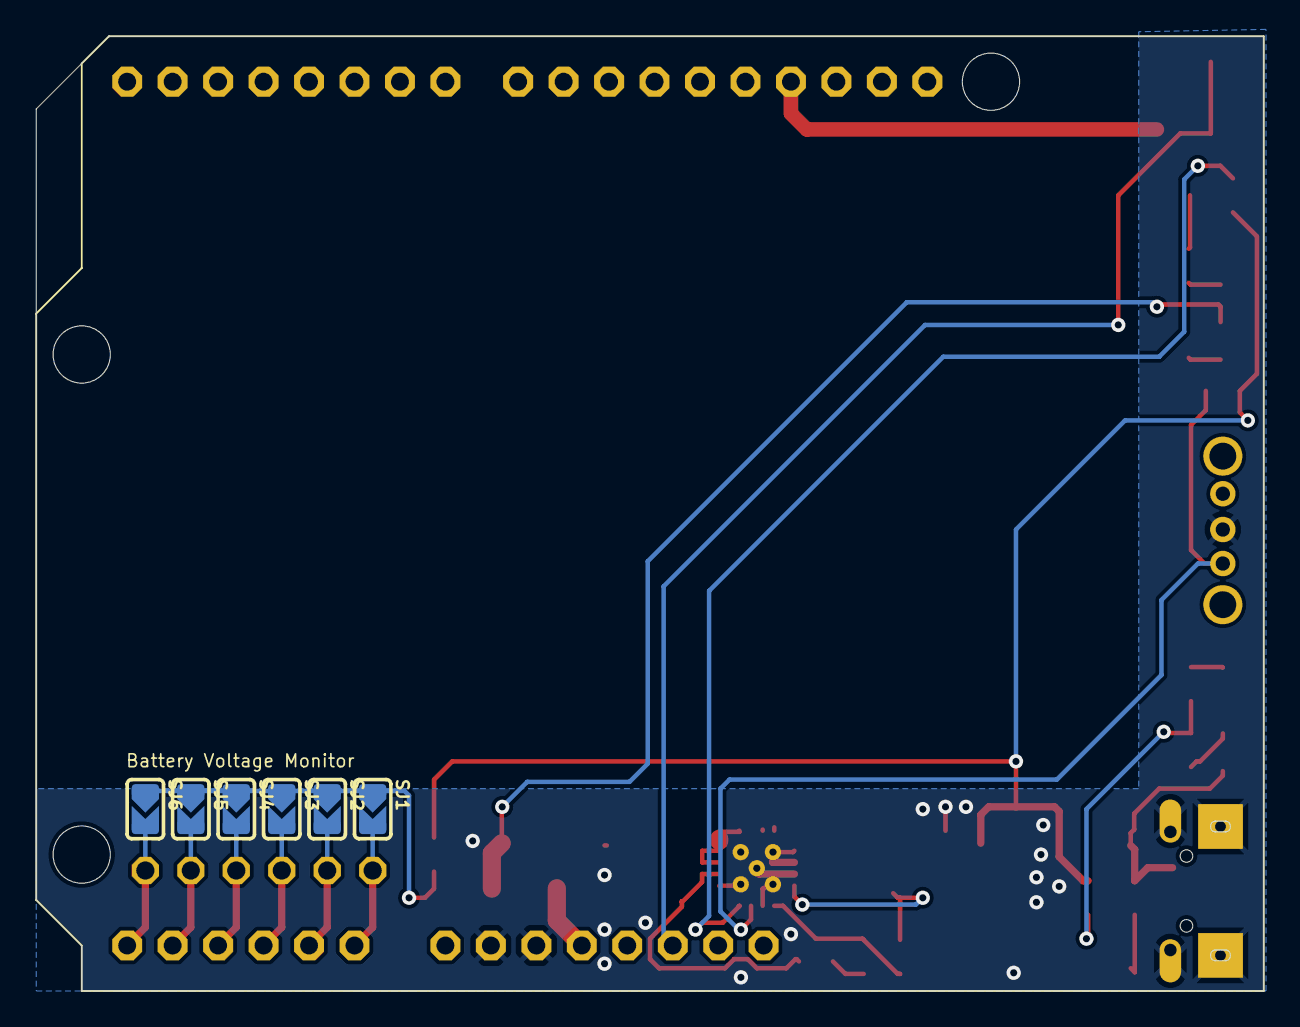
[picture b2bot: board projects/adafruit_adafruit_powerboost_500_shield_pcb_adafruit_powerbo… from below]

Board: 16 copper layers, 68.6 x 53.3 mm, 44 parts (6 on the bottom side), 26 nets.

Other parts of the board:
@HOLE0, @HOLE1, @HOLE2: (no value)
U$6: ADAFRUIT_TEXT_30MM

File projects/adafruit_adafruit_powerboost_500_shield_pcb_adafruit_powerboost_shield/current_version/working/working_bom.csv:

"Id";"Designator";"Footprint";"Quantity";"Designation";"Supplier and ref";
1;"LED3";"CHIPLED_0805_NOOUTLINE";1;"BLUE";;;
2;"R9,R14";"0805-NO";2;"1.87Mohm";;;
3;"R11,R23";"0805-NO";2;"340K";;;
4;"@HOLE0,@HOLE1,@HOLE2";"";3;"";;;
5;"S1";"OS102011MA1Q";1;"OS102011MA1Q";;;
6;"LED1";"CHIPLED_0805_NOOUTLINE";1;"YELLOW";;;
7;"D1";"SOD-123";1;"MBR120";;;
8;"U4";"PVQFN-16";1;"TPS61030RSAR";;;
9;"R10";"0805-NO";1;"200K";;;
10;"T1";"SC59-BEC";1;"MMUN2133LT1G";;;
11;"C9";"EIA3528-21_B-R";1;"100uF/6V";;;
12;"R5,R20,R3";"0805-NO";3;"1K";;;
13;"R1";"0805-NO";1;"470";;;
14;"U$4,U$3";"FIDUCIAL_1MM";2;"FIDUCIAL";;;
15;"R4,R2";"0805-NO";2;"2K";;;
16;"C4";"0805-NO";1;"10µF";;;
17;"U$6";"ADAFRUIT_TEXT_30MM";1;"";;;
18;"F1";"R1206";1;"500mA";;;
19;"L1";"INDUCTOR_5X5MM_TDK_VLC5045";1;"VLC5045-6.8uH";;;
20;"X1";"4UCONN_20329";1;"MicroUSB";;;
21;"C8";"0805-NO";1;"0.1uF";;;
22;"ANALOG0";"1X06";1;"ANALOG";;;
23;"LED2";"CHIPLED_0805_NOOUTLINE";1;"GREEN";;;
24;"U3";"SOT23-5";1;"MCP73831T-2ACI/OT";;;
25;"C6";"0805-NO";1;"10uF";;;
26;"U2";"ARDUINOR3-NOSILK";1;"ARDUINOR3-NOSILK";;;
27;"SW1";"KMR2";1;"SPST_TACT-KMR2";;;
28;"BATT_IN0";"JST-PH-2-SMT";1;"JST-PH";;;
29;"LED4";"CHIPLED_0805_NOOUTLINE";1;"RED";;;
30;"C7";"0805-NO";1;"2.2uF";;;
31;"SJ2,SJ1,SJ6,SJ4,SJ5,SJ3";"SOLDERJUMPER_ARROW_NOPASTE";6;"";;;

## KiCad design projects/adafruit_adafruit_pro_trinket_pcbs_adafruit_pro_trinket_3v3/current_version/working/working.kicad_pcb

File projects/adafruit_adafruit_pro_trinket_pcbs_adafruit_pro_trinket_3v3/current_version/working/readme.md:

# adafruit_pro_trinket_pcbs
 
## summary 
* id: adafruit_adafruit_pro_trinket_pcbs_adafruit_pro_trinket_3v3
* user: adafruit
* name: adafruit_pro_trinket_pcbs
* board: adafruit_pro_trinket_3v3
* repo: https://github.com/adafruit/Adafruit-Pro-Trinket-PCBs

* src_file_repo_sch: 
* src_file_repo_sch_link: https://github.com/adafruit/Adafruit-Pro-Trinket-PCBs/tree/master/
* full details link: https://github.com/oomlout/oomlout_oomp_project_bot_v_2/tree/main/projects/adafruit_adafruit_pro_trinket_pcbs_adafruit_pro_trinket_3v3/current_version/working  

## schematic  
  
[schematic (pdf)](working_schematic.pdf) 

## pcb  

[board (pdf)](working.pdf)  

## working_bom
| Id | Designator | Footprint | Quantity | Designation | Supplier and ref |  | None | 
| --- | --- | --- | --- | --- | --- | --- | --- | 
| 1 | IC2 | SOT23-5L | 1 | MIC5225-3.3v |  |  | [''] | 
| 2 | D2,D3 | SOD-123FL | 2 | SCHOTTKY |  |  | [''] | 
| 3 | JP2 | 1X02_ROUND | 1 |  |  |  | [''] | 
| 4 | @HOLE1,@HOLE2,@HOLE0 |  | 3 |  |  |  | [''] | 
| 5 | IC1 | MLF32-TH | 1 | ATmega328P |  |  | [''] | 
| 6 | U$1,U$6 | FIDUCIAL_1MM | 2 | FIDUCIAL |  |  | [''] | 
| 7 | C2 | _0805MP | 1 | 0.1uF |  |  | [''] | 
| 8 | CN1 | 4UCONN_20329 | 1 |  |  |  | [''] | 
| 9 | R3 | 0603-NO | 1 | 1.5K (0603) |  |  | [''] | 
| 10 | R4,R5 | 0603-NO | 2 | 470 (0603) |  |  | [''] | 
| 11 | JP4,JP1 | 1X12-CB | 2 |  |  |  | [''] | 
| 12 | Y1 | RESONATOR-SMD | 1 | 12MHz |  |  | [''] | 
| 13 | U$7 | ADAFRUIT_3.5MM | 1 |  |  |  | [''] | 
| 14 | C3 | 0805-NO | 1 | 0.1uF |  |  | [''] | 
| 15 | PWR0 | CHIPLED_0805_NOOUTLINE | 1 | green |  |  | [''] | 
| 16 | Q1 | BTN_KMR2_4.6X2.8 | 1 | reset |  |  | [''] | 
| 17 | R1,R2 | 0603-NO | 2 | 68 (0603) |  |  | [''] | 
| 18 | C1,C8 | 0805-NO | 2 | 10uF |  |  | [''] | 
| 19 | B1 | CHIPLED_0805_NOOUTLINE | 1 | red |  |  | [''] | 
| 20 | R6 | 0805-NO | 1 | 10K (0603) |  |  | [''] | 
| 21 | FTDI0 | 1X06-CLEANBIG | 1 |  |  |  | [''] | 
| 22 | U$9 | ADAFRUIT_9MM | 1 |  |  |  | [''] | 
| 23 | BAT0 | JSTPH2 | 1 |  |  |  | [''] | 

## bom_schematic
| Ref | Qnty | Value | Cmp name | Footprint | Description | Vendor | DNP | 
| --- | --- | --- | --- | --- | --- | --- | --- | 
| B1 | 1 | red | LED0805_NOOUTLINE | working:CHIPLED_0805_NOOUTLINE |  |  |  | 
| BAT0 | 1 | CON_JST_PH_2PIN | CON_JST_PH_2PIN | working:JSTPH2 |  |  |  | 
| C1, C8 | 2 | 10uF | CAP_CERAMIC0805-NOOUTLINE | working:0805-NO |  |  |  | 
| C2 | 1 | 0.1uF | CAP_CERAMIC_0805MP | working:_0805MP |  |  |  | 
| C3 | 1 | 0.1uF | CAP_CERAMIC0805-NOOUTLINE | working:0805-NO |  |  |  | 
| CN1 | 1 | USBMICRO_20329 | USBMICRO_20329 | working:4UCONN_20329 |  |  |  | 
| D2, D3 | 2 | SCHOTTKY | DIODE_SOD-123FL | working:SOD-123FL |  |  |  | 
| FTDI0 | 1 | PINHD-1X6CB | PINHD-1X6CB | working:1X06-CLEANBIG |  |  |  | 
| IC1 | 1 | MEGA8-MI | MEGA8-MI | working:MLF32-TH |  |  |  | 
| IC2 | 1 | LP298XS | LP298XS | working:SOT23-5L |  |  |  | 
| JP1, JP4 | 2 | PINHD-1X12-CB | PINHD-1X12-CB | working:1X12-CB |  |  |  | 
| JP2 | 1 | HEADER-1X2ROUND | HEADER-1X2ROUND | working:1X02_ROUND |  |  |  | 
| PWR0 | 1 | green | LED0805_NOOUTLINE | working:CHIPLED_0805_NOOUTLINE |  |  |  | 
| Q1 | 1 | reset | SWITCH_TACT_SMT4.6X2.8 | working:BTN_KMR2_4.6X2.8 |  |  |  | 
| R1, R2 | 2 | 68 (0603) | RESISTOR_0603_NOOUT | working:0603-NO |  |  |  | 
| R3 | 1 | 1.5K (0603) | RESISTOR_0603_NOOUT | working:0603-NO |  |  |  | 
| R4, R5 | 2 | 470 (0603) | RESISTOR_0603_NOOUT | working:0603-NO |  |  |  | 
| R6 | 1 | 10K (0603) | RESISTOR0805_NOOUTLINE | working:0805-NO |  |  |  | 
| U$1, U$6 | 2 | FIDUCIAL | FIDUCIAL | working:FIDUCIAL_1MM |  |  |  | 
| Y1 | 1 | RESONATORSMD | RESONATORSMD | working:RESONATOR-SMD |  |  |  |

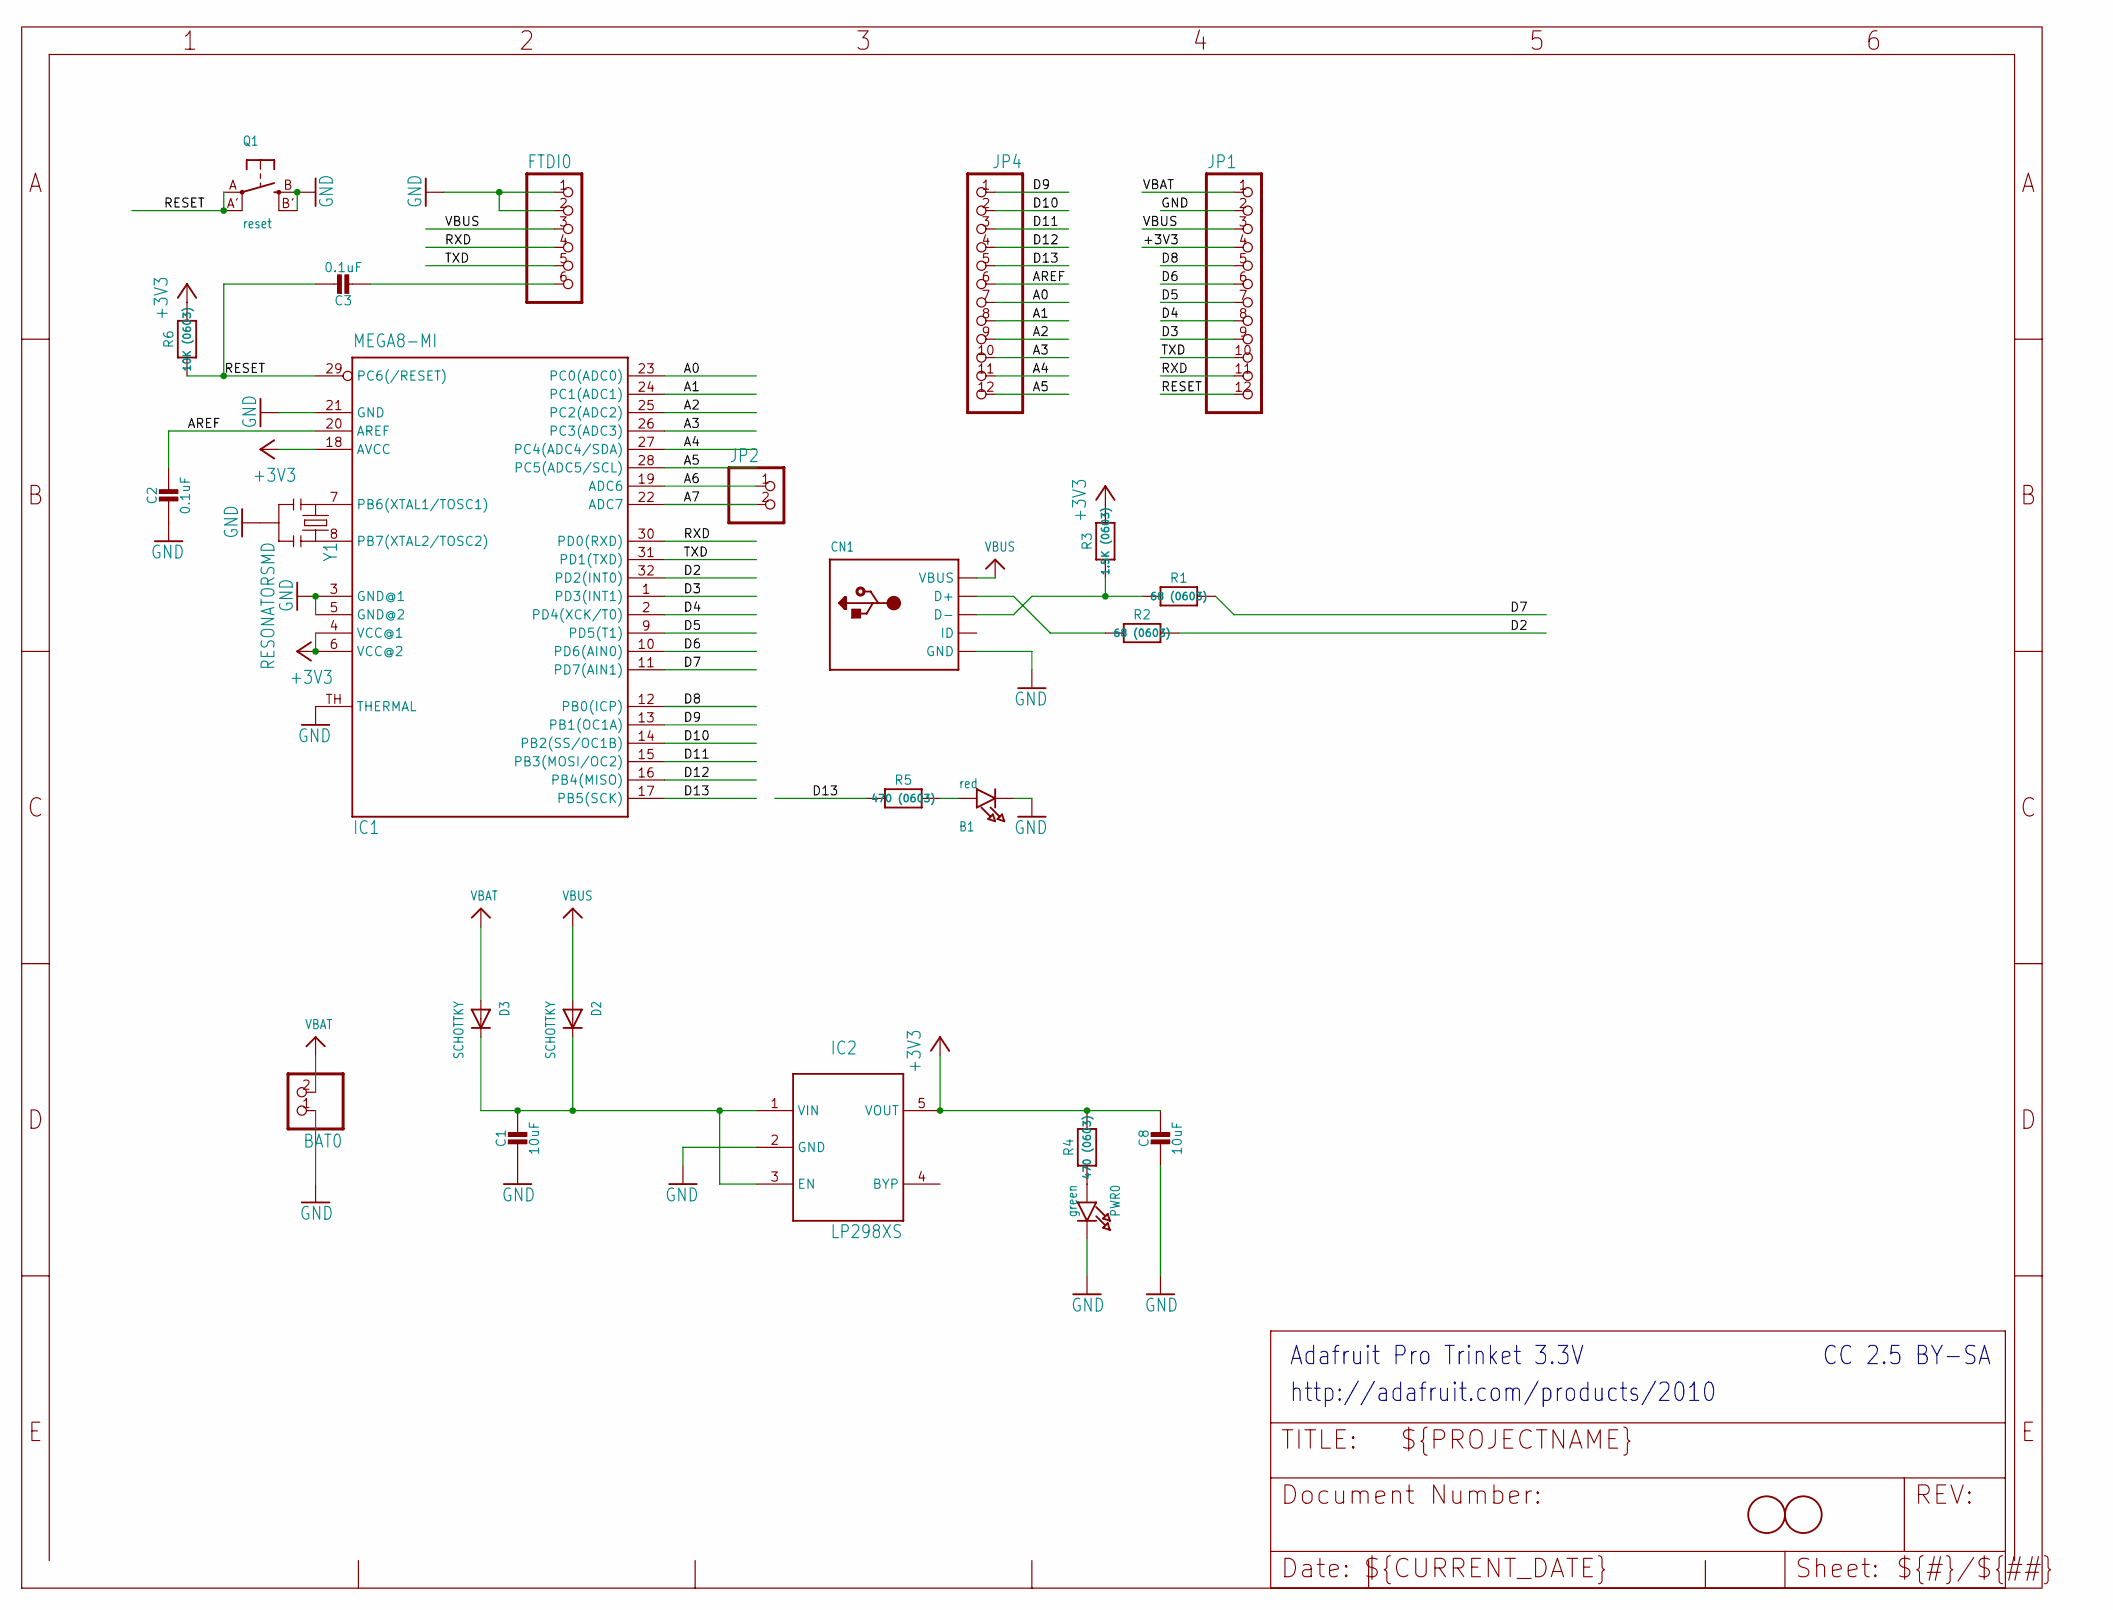
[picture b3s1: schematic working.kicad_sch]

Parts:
B1: red; CHIPLED_0805_NOOUTLINE
BAT0: CON_JST_PH_2PIN; JSTPH2
C1, C8: 10uF; 0805-NO
C2: 0.1uF; _0805MP
C3: 0.1uF; 0805-NO
CN1: USBMICRO_20329; 4UCONN_20329
D2, D3: SCHOTTKY; SOD-123FL
FTDI0: PINHD-1X6CB; 1X06-CLEANBIG
IC1: MEGA8-MI; MLF32-TH
IC2: LP298XS; SOT23-5L
JP1, JP4: PINHD-1X12-CB; 1X12-CB
JP2: HEADER-1X2ROUND; 1X02_ROUND
PWR0: green; CHIPLED_0805_NOOUTLINE
Q1: reset; BTN_KMR2_4.6X2.8
R1, R2: 68 (0603); 0603-NO
R3: 1.5K (0603); 0603-NO
R4, R5: 470 (0603); 0603-NO
R6: 10K (0603); 0805-NO
U$1, U$6: FIDUCIAL; FIDUCIAL_1MM
Y1: RESONATORSMD; RESONATOR-SMD

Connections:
+3V3: C8.1, IC1.4 (VCC@1), IC1.6 (VCC@2), IC1.18 (AVCC), IC2.5 (VOUT), JP1.4, R3.2, R4.2, R6.2
A0: IC1.23 (PC0(ADC0)), JP4.7
A1: IC1.24 (PC1(ADC1)), JP4.8
A2: IC1.25 (PC2(ADC2)), JP4.9
A3: IC1.26 (PC3(ADC3)), JP4.10
A4: IC1.27 (PC4(ADC4/SDA)), JP4.11
A5: IC1.28 (PC5(ADC5/SCL)), JP4.12
A6: IC1.19 (ADC6), JP2.1
A7: IC1.22 (ADC7), JP2.2
AREF: C2.1, IC1.20 (AREF), JP4.6
D2: IC1.32 (PD2(INT0)), R2.2
D3: IC1.1 (PD3(INT1)), JP1.9
D4: IC1.2 (PD4(XCK/T0)), JP1.8
D5: IC1.9 (PD5(T1)), JP1.7
D6: IC1.10 (PD6(AIN0)), JP1.6
D7: IC1.11 (PD7(AIN1)), R1.2
D8: IC1.12 (PB0(ICP)), JP1.5
D9: IC1.13 (PB1(OC1A)), JP4.1
D10: IC1.14 (PB2(SS/OC1B)), JP4.2
D11: IC1.15 (PB3(MOSI/OC2)), JP4.3
D12: IC1.16 (PB4(MISO)), JP4.4
D13: IC1.17 (PB5(SCK)), JP4.5, R5.2
D+: CN1.D+, R2.1
D-: CN1.D-, R1.1, R3.1
DTR/RTS: C3.2, FTDI0.6
GND: B1.C, BAT0.1, C1.2, C2.2, C8.2, CN1.BASE@1 (GND), CN1.BASE@2 (GND), CN1.GND, CN1.SPRT@1 (GND), CN1.SPRT@2 (GND), CN1.SPRT@3 (GND), CN1.SPRT@4 (GND), FTDI0.1, FTDI0.2, IC1.3 (GND@1), IC1.5 (GND@2), IC1.21 (GND), IC1.TH (THERMAL), IC2.2 (GND), JP1.2, PWR0.C, Q1.B (S), Q1.B' (S1), Y1.2
unnamed: B1.A, R5.1
unnamed: IC1.8 (PB7(XTAL2/TOSC2)), Y1.3
unnamed: IC1.7 (PB6(XTAL1/TOSC1)), Y1.1
unnamed: PWR0.A, R4.1
unnamed: C1.1, D2.C, D3.C, IC2.1 (VIN), IC2.3 (EN)
RESET: C3.1, IC1.29 (PC6(/RESET)), JP1.12, Q1.A, Q1.A' (P1), R6.1
RXD: FTDI0.4, IC1.30 (PD0(RXD)), JP1.11
TXD: FTDI0.5, IC1.31 (PD1(TXD)), JP1.10
VBAT: BAT0.2, D3.A, JP1.1
VBUS: CN1.VBUS, D2.A, FTDI0.3, JP1.3

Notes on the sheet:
CC 2.5 BY-SA
http://adafruit.com/products/2010
Adafruit Pro Trinket 3.3V

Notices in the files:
projects/adafruit_adafruit_prototyping_pi_plate_pcb_adafruit_proto_pi_plate/current_version/working/working.kicad_pcb:
Copyright (c) 2012
CERN OHL v1.1
Licenced under
B.Cu
